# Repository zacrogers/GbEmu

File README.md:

## Mini handheld
- ESP32

### Zephyr project

` west update `

- states
- subsystems
- connectivity
- games
- utilities

### Electronics
- V1

## Gameboy Emulator - WIP

Following tutorial at  https://www.youtube.com/watch?v=e87qKixKFME

Important References:

https://gbdev.io/pandocs/

https://www.pastraiser.com/cpu/gameboy/gameboy_opcodes.html

https://archive.org/details/GameBoyProgManVer1.1/page/n85/mode/2up

https://github.com/rockytriton/LLD_gbemu/raw/main/docs/The%20Cycle-Accurate%20Game%20Boy%20Docs.pdf

https://github.com/rockytriton/LLD_gbemu/raw/main/docs/gbctr.pdf

Current progress PART 02:
    NEED TO FIX!!!

    zac@zac-iMac:~/Documents/GbEmu/my_emu/build$ gbemu/gbemu  ../../roms/dmg-acid2.gb
    Opened: ../../roms/dmg-acid2.gb
    Cartridge Loaded:
            Title    : DMG-ACID2
            Type     : 00 (ROM ONLY)
            ROM Size : 32 KB
            RAM Size : 00
            LIC Code : 00 (None)
            ROM Vers : 00
            Checksum : 9F (PASSED)
    Cart loaded..
    SDL INIT
    TTF INIT
    Exectuting instruction 00    PC: 0101
    Not executing yet...
    Unknown addressing mode: 14

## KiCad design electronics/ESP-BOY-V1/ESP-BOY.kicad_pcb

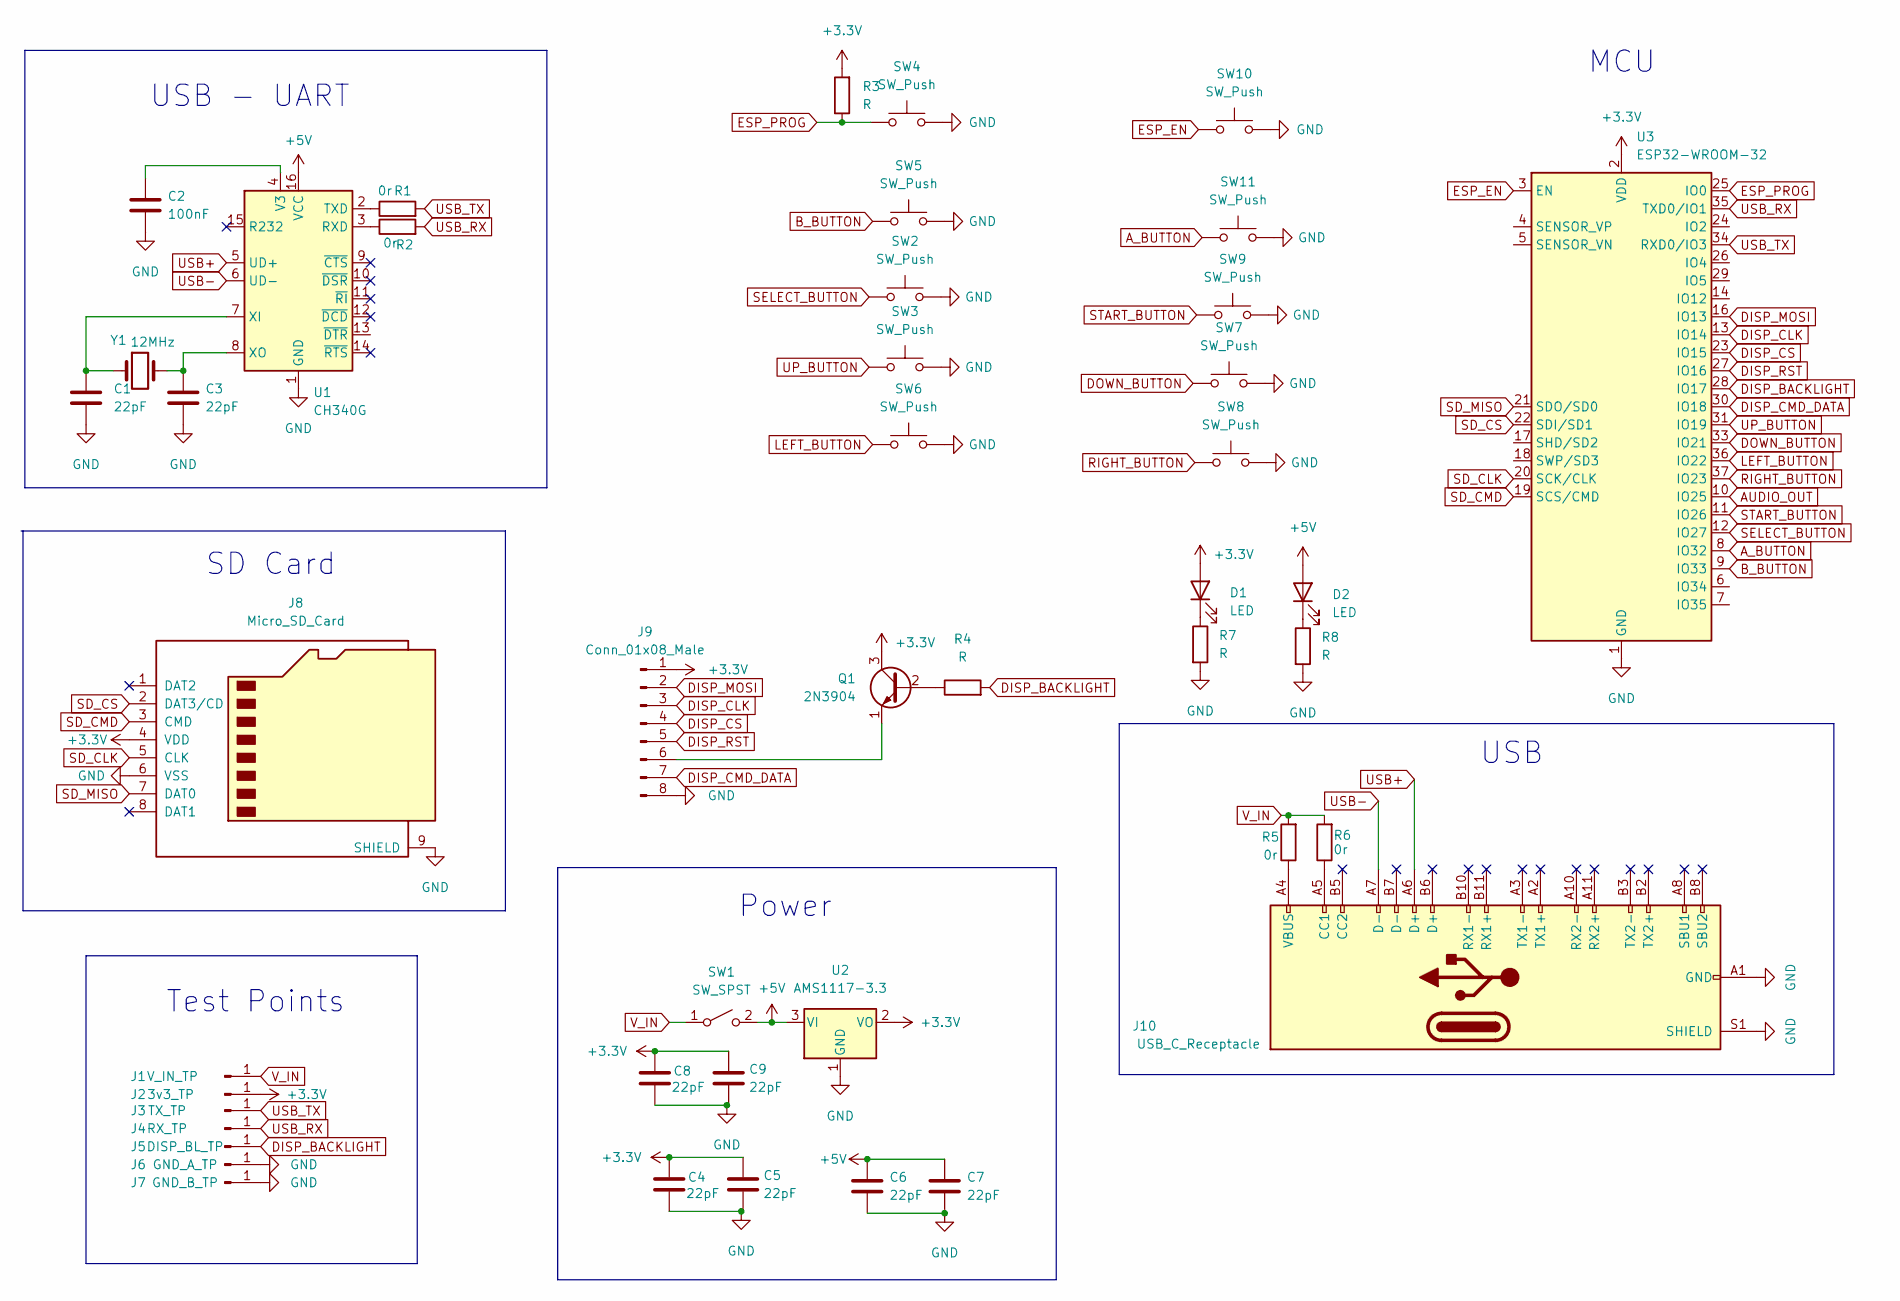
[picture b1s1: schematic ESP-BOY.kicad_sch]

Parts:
C1, C3, C4, C5, C6, C7, C8, C9: 22pF; C_0805_2012Metric
C2: 100nF; C_0805_2012Metric
D1, D2: LED; LED_1206_3216Metric
J1: V_IN_TP; PinSocket_1x01_P2.54mm_Vertical
J2: 3v3_TP; PinSocket_1x01_P2.54mm_Vertical
J3: TX_TP; PinSocket_1x01_P2.54mm_Vertical
J4: RX_TP; PinSocket_1x01_P2.54mm_Vertical
J5: DISP_BL_TP; PinSocket_1x01_P2.54mm_Vertical
J6: GND_A_TP; PinSocket_1x01_P2.54mm_Vertical
J7: GND_B_TP; PinSocket_1x01_P2.54mm_Vertical
J8: Micro_SD_Card; microSD_HC_Wuerth_693072010801
J9: Conn_01x08_Male; PinSocket_1x08_P2.54mm_Vertical
J10: USB_C_Receptacle; USB_C_Receptacle_Amphenol_12401548E4-2A
Q1: 2N3904; SOT-23
R1, R2, R5, R6: 0r; R_0805_2012Metric
R3, R4, R7, R8: R; R_0805_2012Metric
SW1: SW_SPST; SW_SPST_CK_KXT3
SW2, SW3, SW4, SW5, SW6, SW7, SW8, SW9, SW10, SW11: SW_Push; SW_SPST_CK_KXT3
U1: CH340G; SOIC-16_3.9x9.9mm_P1.27mm
U2: AMS1117-3.3; SOT-223-3_TabPin2
U3: ESP32-WROOM-32
Y1: 12MHz; Crystal_SMD_0603-4Pin_6.0x3.5mm_HandSoldering

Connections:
+3V3: C4.1, C5.1, C8.1, C9.1, D1.2 (A), J2.1, J8.4 (VDD), J9.1, Q1.3 (C), R3.2, U2.2 (VO), U3.2 (VDD)
AUDIO_OUT: U3.10 (IO25)
A_BUTTON: SW11.1, U3.8 (IO32)
B_BUTTON: SW5.1, U3.9 (IO33)
DISP_BACKLIGHT: J5.1, R4.2, U3.28 (IO17)
DISP_CLK: J9.3, U3.13 (IO14)
DISP_CMD_DATA: J9.7, U3.30 (IO18)
DISP_CS: J9.4, U3.23 (IO15)
DISP_MOSI: J9.2, U3.16 (IO13)
DISP_RST: J9.5, U3.27 (IO16)
DOWN_BUTTON: SW7.1, U3.33 (IO21)
ESP_EN: SW10.1, U3.3 (EN)
ESP_PROG: R3.1, SW4.1, U3.25 (IO0)
GND: C1.2, C2.2, C3.2, C4.2, C5.2, C6.2, C7.2, C8.2, C9.2, J6.1, J7.1, J8.6 (VSS), J8.9 (SHIELD), J9.8, J10.A1 (GND), J10.A12 (GND), J10.B1 (GND), J10.B12 (GND), J10.S1 (SHIELD), R7.2, R8.2, SW2.2, SW3.2, SW4.2, SW5.2, SW6.2, SW7.2, SW8.2, SW9.2, SW10.2, SW11.2, U1.1 (GND), U2.1 (GND), U3.1 (GND), U3.15 (GND), U3.38 (GND), U3.39 (GND)
LEFT_BUTTON: SW6.1, U3.36 (IO22)
unnamed: C1.1, U1.7 (XI), Y1.1
unnamed: C2.1, U1.4 (V3)
unnamed: C3.1, U1.8 (XO), Y1.2
unnamed: D1.1 (K), R7.1
unnamed: D2.1 (K), R8.1
unnamed: J9.6, Q1.1 (E)
unnamed: J10.A4 (VBUS), J10.A9 (VBUS), J10.B4 (VBUS), J10.B9 (VBUS), R5.1
unnamed: J10.A5 (CC1), R6.1
unnamed: Q1.2 (B), R4.1
unnamed: R1.1, U1.2 (TXD)
unnamed: R2.1, U1.3 (RXD)
RIGHT_BUTTON: SW8.1, U3.37 (IO23)
SD_CLK: J8.5 (CLK), U3.20 (SCK/CLK)
SD_CMD: J8.3 (CMD), U3.19 (SCS/CMD)
SD_CS: J8.2 (DAT3/CD), U3.22 (SDI/SD1)
SD_MISO: J8.7 (DAT0), U3.21 (SDO/SD0)
SELECT_BUTTON: SW2.1, U3.12 (IO27)
START_BUTTON: SW9.1, U3.11 (IO26)
UP_BUTTON: SW3.1, U3.31 (IO19)
USB+: J10.A6 (D+), U1.5 (UD+)
USB-: J10.A7 (D-), U1.6 (UD-)
USB_RX: J4.1, R2.2, U3.35 (TXD0/IO1)
USB_TX: J3.1, R1.2, U3.34 (RXD0/IO3)
V_IN: J1.1, R5.2, R6.2, SW1.1 (A)

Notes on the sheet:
USB
Test Points
SD Card
USB - UART
Power
MCU

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
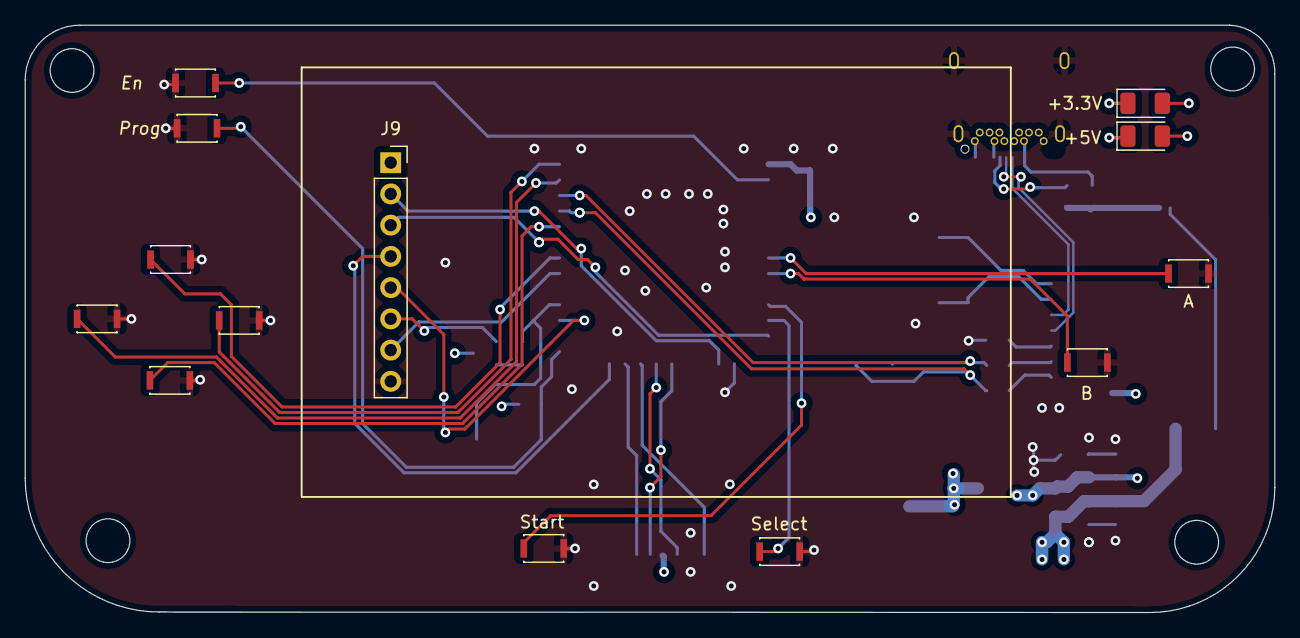
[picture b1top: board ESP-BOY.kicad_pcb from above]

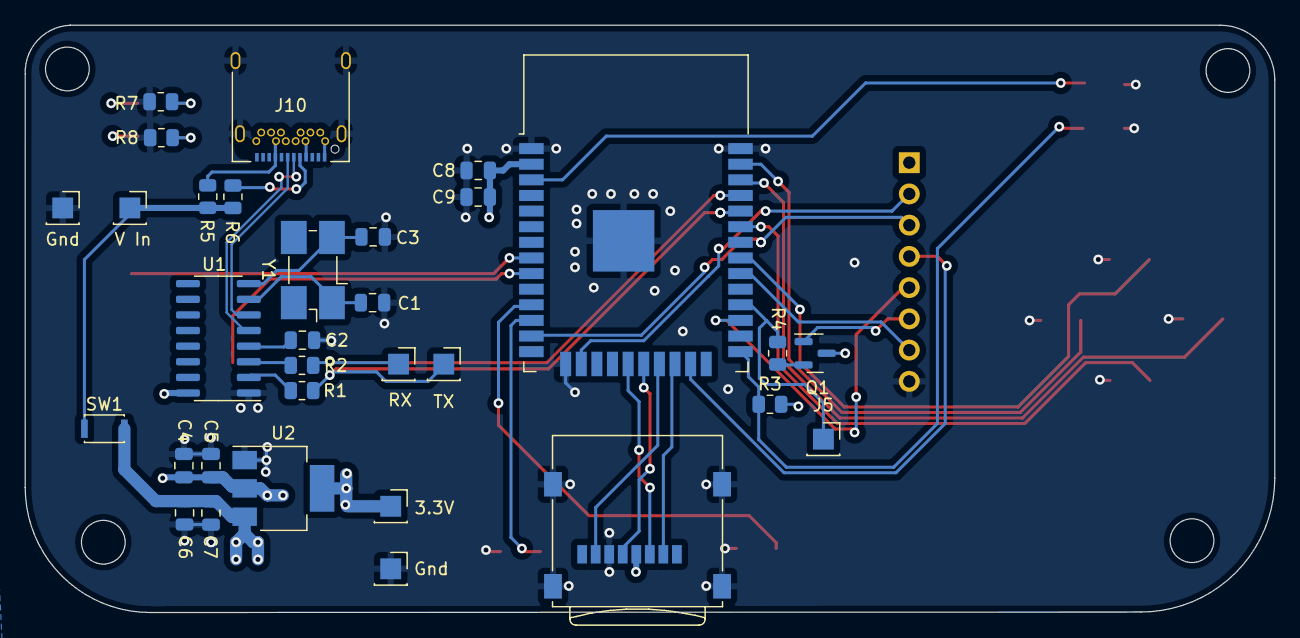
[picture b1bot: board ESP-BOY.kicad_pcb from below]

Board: 4 copper layers, 101.6 x 47.8 mm, 45 parts (32 on the bottom side), 39 nets.

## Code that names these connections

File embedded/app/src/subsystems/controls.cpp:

#include "../../inc/subsystems/controls.hh"

#include <zephyr/logging/log.h>
LOG_MODULE_REGISTER(controls, LOG_LEVEL_DBG);


struct gpio_callback            Controls::cb_data[InputType::NUM_INPUTS]          { };
struct k_timer                  Controls::button_timers[InputType::NUM_INPUTS]    { };
uint64_t                        Controls::last_time[InputType::NUM_INPUTS]        { };
etl::queue<Controls::InputType, Controls::INPUT_QUEUE_SIZE> Controls::input_queue { };

Controls::TriggerType           Controls::trigger_mapping[InputType::NUM_INPUTS]  {
    [InputType::A]      = Controls::TriggerType::ONE_SHOT,
    [InputType::B]      = Controls::TriggerType::ONE_SHOT,
    [InputType::START]  = Controls::TriggerType::ONE_SHOT,
    [InputType::SELECT] = Controls::TriggerType::ONE_SHOT,
    [InputType::UP]     = Controls::TriggerType::PERIODIC,
    [InputType::DOWN]   = Controls::TriggerType::PERIODIC,
    [InputType::LEFT]   = Controls::TriggerType::ONE_SHOT,
    [InputType::RIGHT]  = Controls::TriggerType::ONE_SHOT
};


struct gpio_dt_spec Controls::button[InputType::NUM_INPUTS] {
    GPIO_DT_SPEC_GET(DT_NODELABEL(a_button),      gpios),
    GPIO_DT_SPEC_GET(DT_NODELABEL(b_button),      gpios),
    GPIO_DT_SPEC_GET(DT_NODELABEL(start_button),  gpios),
    GPIO_DT_SPEC_GET(DT_NODELABEL(select_button), gpios),
    GPIO_DT_SPEC_GET(DT_NODELABEL(up_button),     gpios),
    GPIO_DT_SPEC_GET(DT_NODELABEL(down_button),   gpios),
    GPIO_DT_SPEC_GET(DT_NODELABEL(left_button),   gpios),
    GPIO_DT_SPEC_GET(DT_NODELABEL(right_button),  gpios)
};


#define DEBOUNCE_TIMEOUT_MS 100
#define TIMER_RETRIGGER_MS 50


/*
    Button timer handlers
*/
void Controls::timer_handler(Controls::InputType input)
{
    Controls::input_queue.push(input);

    if(!gpio_pin_get_dt(&button[input]))
    {
        k_timer_stop(&button_timers[input]);
    }
}


void Controls::a_button_timer_handler(struct k_timer *dummy)
{
    Controls::timer_handler(InputType::A);
}


void Controls::b_button_timer_handler(struct k_timer *dummy)
{
   Controls::timer_handler(InputType::B);
}


void Controls::up_button_timer_handler(struct k_timer *dummy)
{
   Controls::timer_handler(InputType::UP);
}


void Controls::down_button_timer_handler(struct k_timer *dummy)
{
   Controls::timer_handler(InputType::DOWN);
}


void Controls::left_button_timer_handler(struct k_timer *dummy)
{
   Controls::timer_handler(InputType::LEFT);
}


void Controls::right_button_timer_handler(struct k_timer *dummy)
{
   Controls::timer_handler(InputType::RIGHT);
}


void Controls::start_button_timer_handler(struct k_timer *dummy)
{
   Controls::timer_handler(InputType::START);
}


void Controls::select_button_timer_handler(struct k_timer *dummy)
{
   Controls::timer_handler(InputType::SELECT);
}


void Controls::clear_queue()
{
}


Controls::Controls()
{
    // Init buttons
    bool a      = init_gpio_pin(InputType::A,      a_button_timer_handler,      a_button_pressed);
    bool b      = init_gpio_pin(InputType::B,      b_button_timer_handler,      b_button_pressed);
    bool up     = init_gpio_pin(InputType::UP,     up_button_timer_handler,     up_button_pressed);
    bool down   = init_gpio_pin(InputType::DOWN,   down_button_timer_handler,   down_button_pressed);
    bool left   = init_gpio_pin(InputType::LEFT,   left_button_timer_handler,   left_button_pressed);
    bool right  = init_gpio_pin(InputType::RIGHT,  right_button_timer_handler,  right_button_pressed);
    bool start  = init_gpio_pin(InputType::START,  start_button_timer_handler,  start_button_pressed);
    bool select = init_gpio_pin(InputType::SELECT, select_button_timer_handler, select_button_pressed);

    LOG_INF("|   Button Status   |\n |-------------------|\n | A | B | UP | DOWN | LEFT | RIGHT |\n| %d | %d | %d  |  %d   | %d | %d |",
            //   START | SELECT |\n \
            //   %d  |  %d   |",
             a, b,
             up, down,
             left, right
            // start, select
    );
}


bool Controls::init_gpio_pin(InputType input, k_timer_expiry_t timer_fn, gpio_callback_handler_t gpio_cb)
{
    if (device_is_ready(button[input].port))
    {
        int ret = gpio_pin_configure_dt(&button[input], GPIO_INPUT);

        ret = gpio_pin_interrupt_configure_dt(&button[input], GPIO_INT_EDGE_TO_ACTIVE);
        gpio_init_callback(&cb_data[input], gpio_cb , BIT(button[input].pin));
        ret = gpio_add_callback(button[input].port, &cb_data[input]);
        k_timer_init(&Controls::button_timers[input], timer_fn, NULL);

        return ret == 0;
    }
    return false;
}


Controls::~Controls()
{

}


const Controls::InputType Controls::get_last_pressed()
{
    if(!input_queue.empty())
    {
        Controls::InputType last_pressed;
        input_queue.pop_into(last_pressed);
        return last_pressed;
    }

    return Controls::InputType::NONE;
}


/*
    Button Handlers
*/
void Controls::handle_button(Controls::InputType input)
{
    uint64_t now = k_uptime_get();
    if ((now - Controls::last_time[input]) > DEBOUNCE_TIMEOUT_MS)
    {
        if(Controls::trigger_mapping[input] == Controls::TriggerType::PERIODIC)
        {
            k_timer_start(&button_timers[input],
                        K_MSEC(TIMER_RETRIGGER_MS),
                        K_MSEC(TIMER_RETRIGGER_MS));
        }
        else if(Controls::trigger_mapping[input] == Controls::TriggerType::ONE_SHOT)
        {
            LOG_DBG("I: %d", input);
            Controls::input_queue.push(input);
        }
    }

    Controls::last_time[input] = now;
}


void Controls::a_button_pressed(const struct device *dev,
                                struct gpio_callback* cb,
                                uint32_t pins)
{
    handle_button(InputType::A);
}

void Controls::b_button_pressed(const struct device *dev,
                                struct gpio_callback* cb,
                                uint32_t pins)
{
    handle_button(InputType::B);

}

void Controls::up_button_pressed(const struct device *dev,
                                    struct gpio_callback* cb,
                                    uint32_t pins)
{
    handle_button(InputType::UP);
}

void Controls::down_button_pressed(const struct device *dev,
                                    struct gpio_callback* cb,
                                    uint32_t pins)
{
    handle_button(InputType::DOWN);
}

void Controls::left_button_pressed(const struct device *dev,
                                    struct gpio_callback* cb,
                                    uint32_t pins)
{
    handle_button(InputType::LEFT);
}

void Controls::right_button_pressed(const struct device *dev,
                                    struct gpio_callback* cb,
                                    uint32_t pins)
{
    handle_button(InputType::RIGHT);
}

void Controls::start_button_pressed(const struct device *dev,
                                    struct gpio_callback* cb,
                                    uint32_t pins)
{
    handle_button(InputType::START);
}

void Controls::select_button_pressed(const struct device *dev,
                                    struct gpio_callback* cb,
                                    uint32_t pins)
{
    handle_button(InputType::SELECT);
}

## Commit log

2021-11-11 Finished part 2 (almost)
2023-06-18 started cpp version
2023-06-18 fleshed out instructions, moved bus and registers
2023-06-18 add emu class, some printing functions
2023-06-19 setup building
2023-06-19 read cart from bus
2023-06-19 add more instructions
2023-06-19 MOAR
2023-06-19 more info tags
2023-06-19 skeleton processes
2023-06-19 tidy
2023-06-19 add more instruction info
2023-06-20 add all instruction info
2023-06-20 realign header
2023-06-20 add more fetch instructions
2023-06-20 add some more
2023-06-21 implement more fetch instructions
2023-06-23 add embedded target
2023-06-23 restructure project
2023-06-23 add desktop platform
2023-06-23 add build script
2023-06-23 use embedded template library
2023-06-24 add draw window
2023-06-24 refactor registers, implment inc, dec
2023-06-24 implement some more processes
2023-07-01 more instructions
2023-07-01 add some drawing
2023-07-01 add more ops
2023-07-01 add flags
2023-07-02 implement more 01-special
2023-07-06 add overlay
2023-07-08 screen sample working: esp32, st7735r 160x128
2023-07-08 stripes
2023-07-08 draw grid
2023-07-08 copy tile draw
2023-07-08 add vram, make colour union
2023-07-08 add gameboy doctor
2023-07-09 fix jump offset
2023-10-13 fixed etl include
2023-10-13 add structure, implement some control logic
2023-10-14 add engine state base class
2023-10-14 fixed build error
2023-10-14 tidy controls class
2023-10-14 tidy state classes
2023-10-15 add more menu stuff
2023-10-15 fill screen
2023-10-17 lvgl working
2023-10-17 move graphics, add game state
2023-10-17 looping ball
2023-10-17 bouncy
2023-10-17 tidy screen bounds collision
2023-10-17 add playstates
2023-10-17 add pos struct, remove redundant code
2023-10-17 track scores, end game
2023-10-17 add button reading
2023-10-27 update emu core
2023-10-28 fix button press detection
2023-10-28 trigger mutiple events on long press
2023-10-28 up down button working
2023-10-28 both paddles work
2023-10-28 move states to folder
2023-10-28 fixed colours, added main page
2023-10-29 screen change working
2023-10-29 game selection dropdown working
2023-11-01 tidy embedded deps
2023-11-01 fix unresponsive screen
2023-11-04 wifi connecting
2023-11-04 move subsystems to folder
2023-11-04 start wifi page
2023-11-04 add more kconfig flags
2023-11-04 add kicad project
2023-11-04 fix include paths
2023-11-05 loading / deleting games working
2023-11-05 Mini handheld (#2)
    * fixed etl include
    * add structure, implement some control logic
    * add engine state base class
    * fixed build error
    * tidy controls class
    * tidy state classes
2023-11-05 remove actions files
2023-11-05 add bluetooth stuff
2023-11-07 finish schematic connections
2023-11-07 start pcb layout
2023-11-07 first routing pass
2023-11-10 did more pcb layout stuff
2023-11-10 add bluetooth demo
2023-11-10 remove bt stuff
2023-11-11 add data logger
2023-11-12 make logger observer
2024-07-24 add rpi picoboard
2024-07-28 add pwm & imu
2024-07-30 led strip
2024-08-03 basic pong running smooth
2024-08-04 fix crash on exit after game over
2024-08-04 change ball direction & speed
2024-08-05 show pong score
2024-08-11 move pong screen initialisers
2024-08-11 add left/reight button handlers
2024-08-11 handle start/select buttons
2024-08-15 menu nav kinda working
2024-08-15 change slider focus
2024-08-15 add slider focus style
2024-08-16 tidy sliders
